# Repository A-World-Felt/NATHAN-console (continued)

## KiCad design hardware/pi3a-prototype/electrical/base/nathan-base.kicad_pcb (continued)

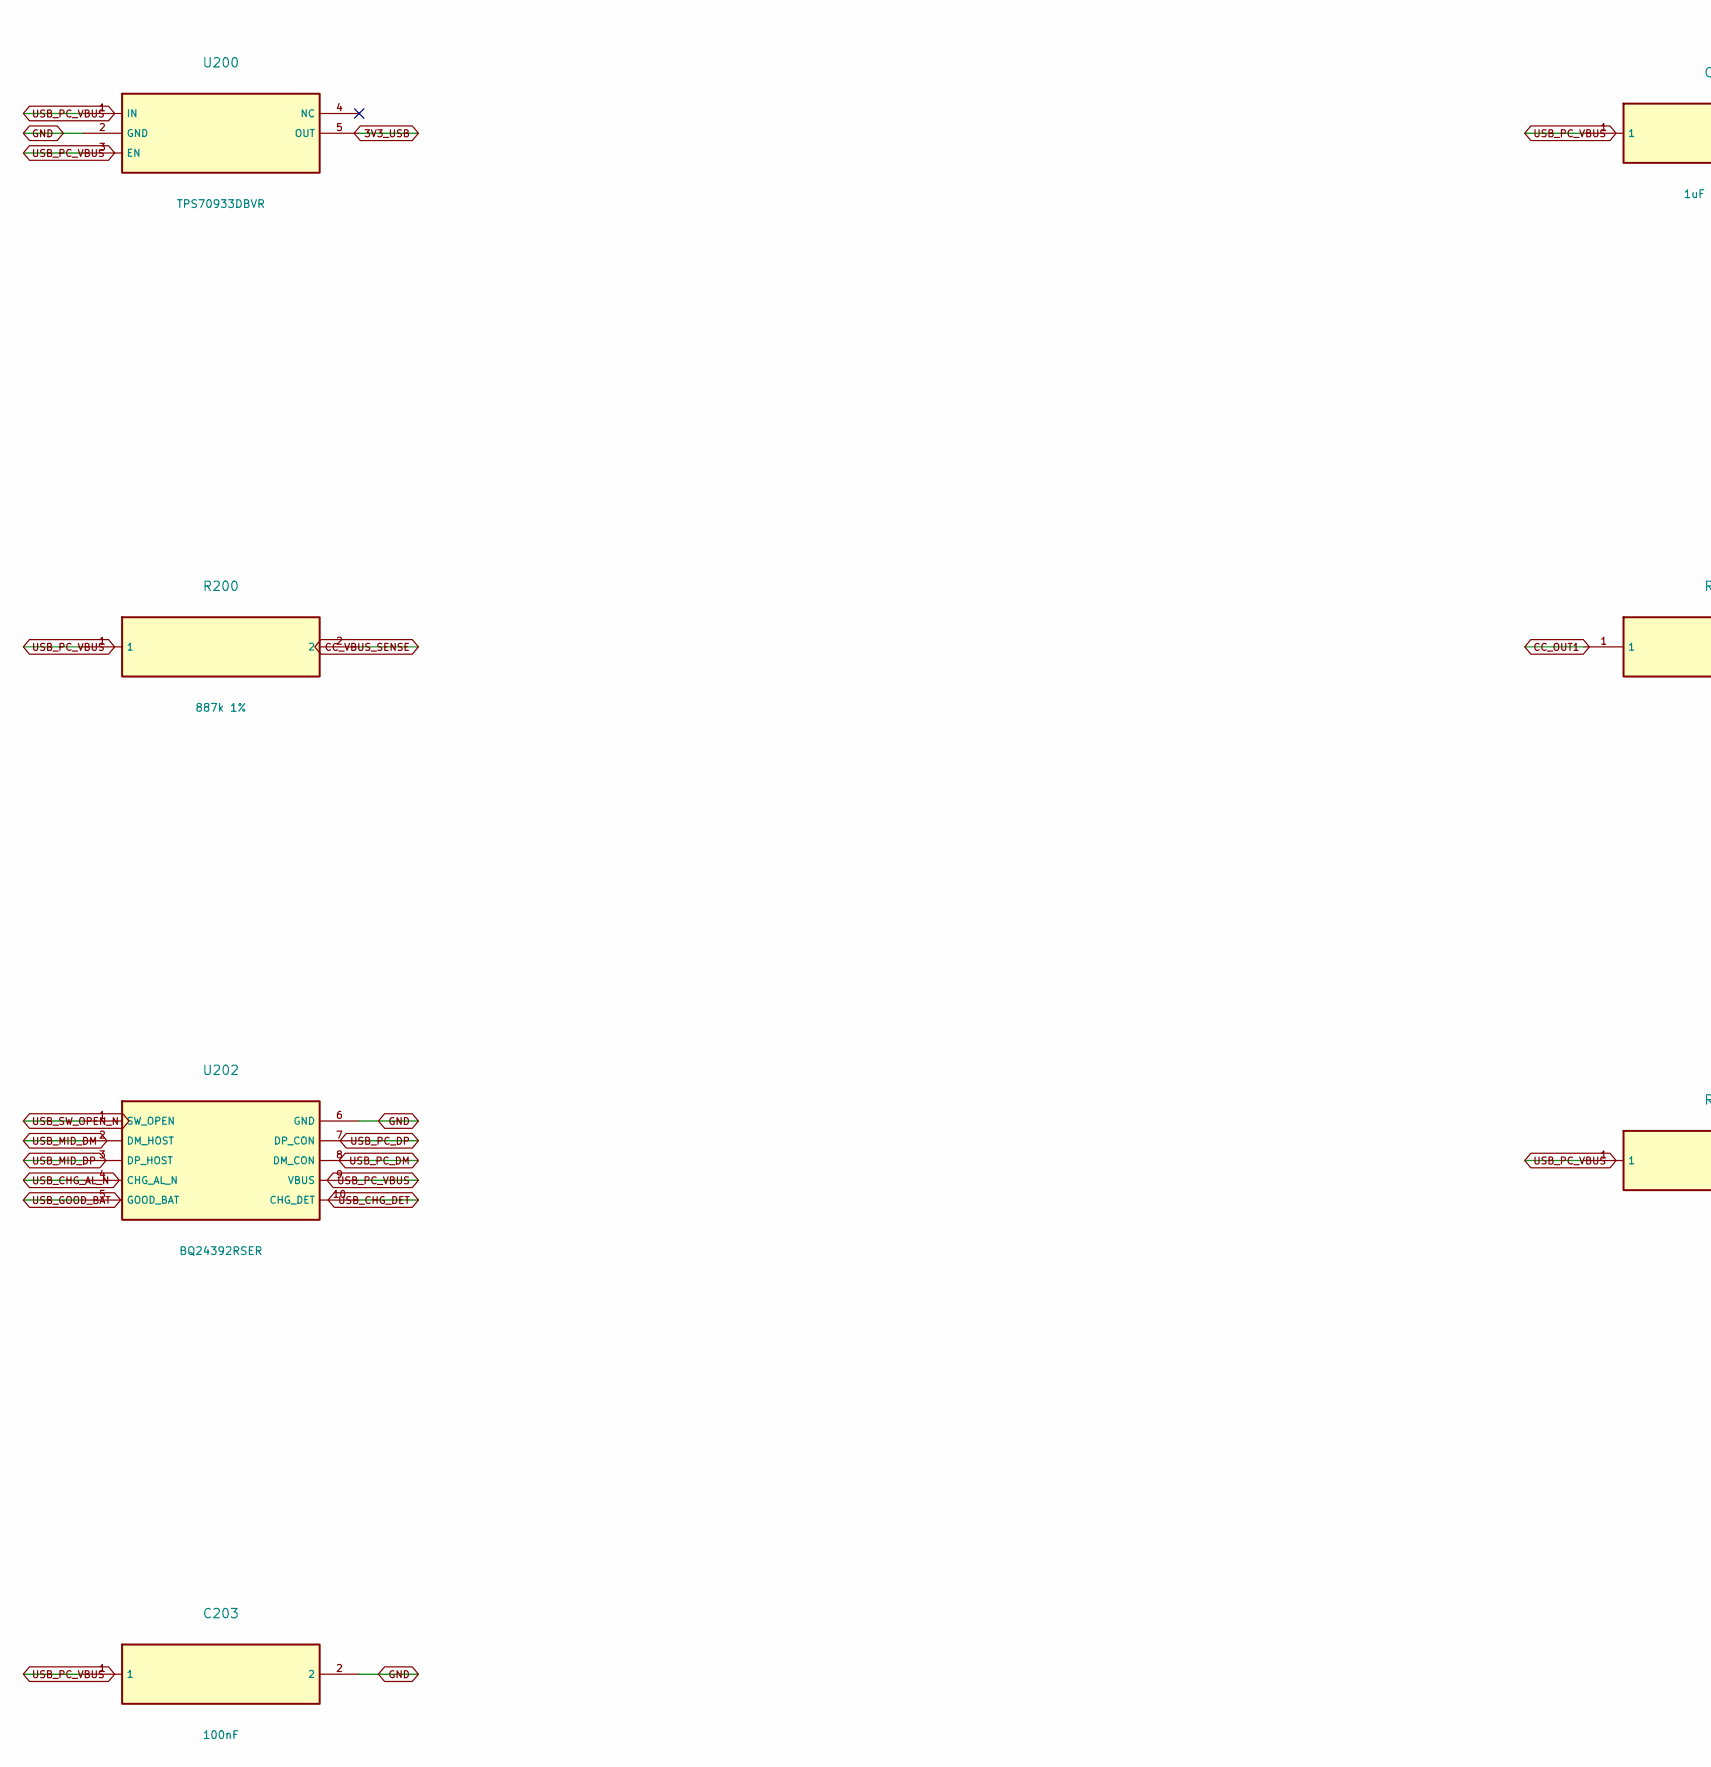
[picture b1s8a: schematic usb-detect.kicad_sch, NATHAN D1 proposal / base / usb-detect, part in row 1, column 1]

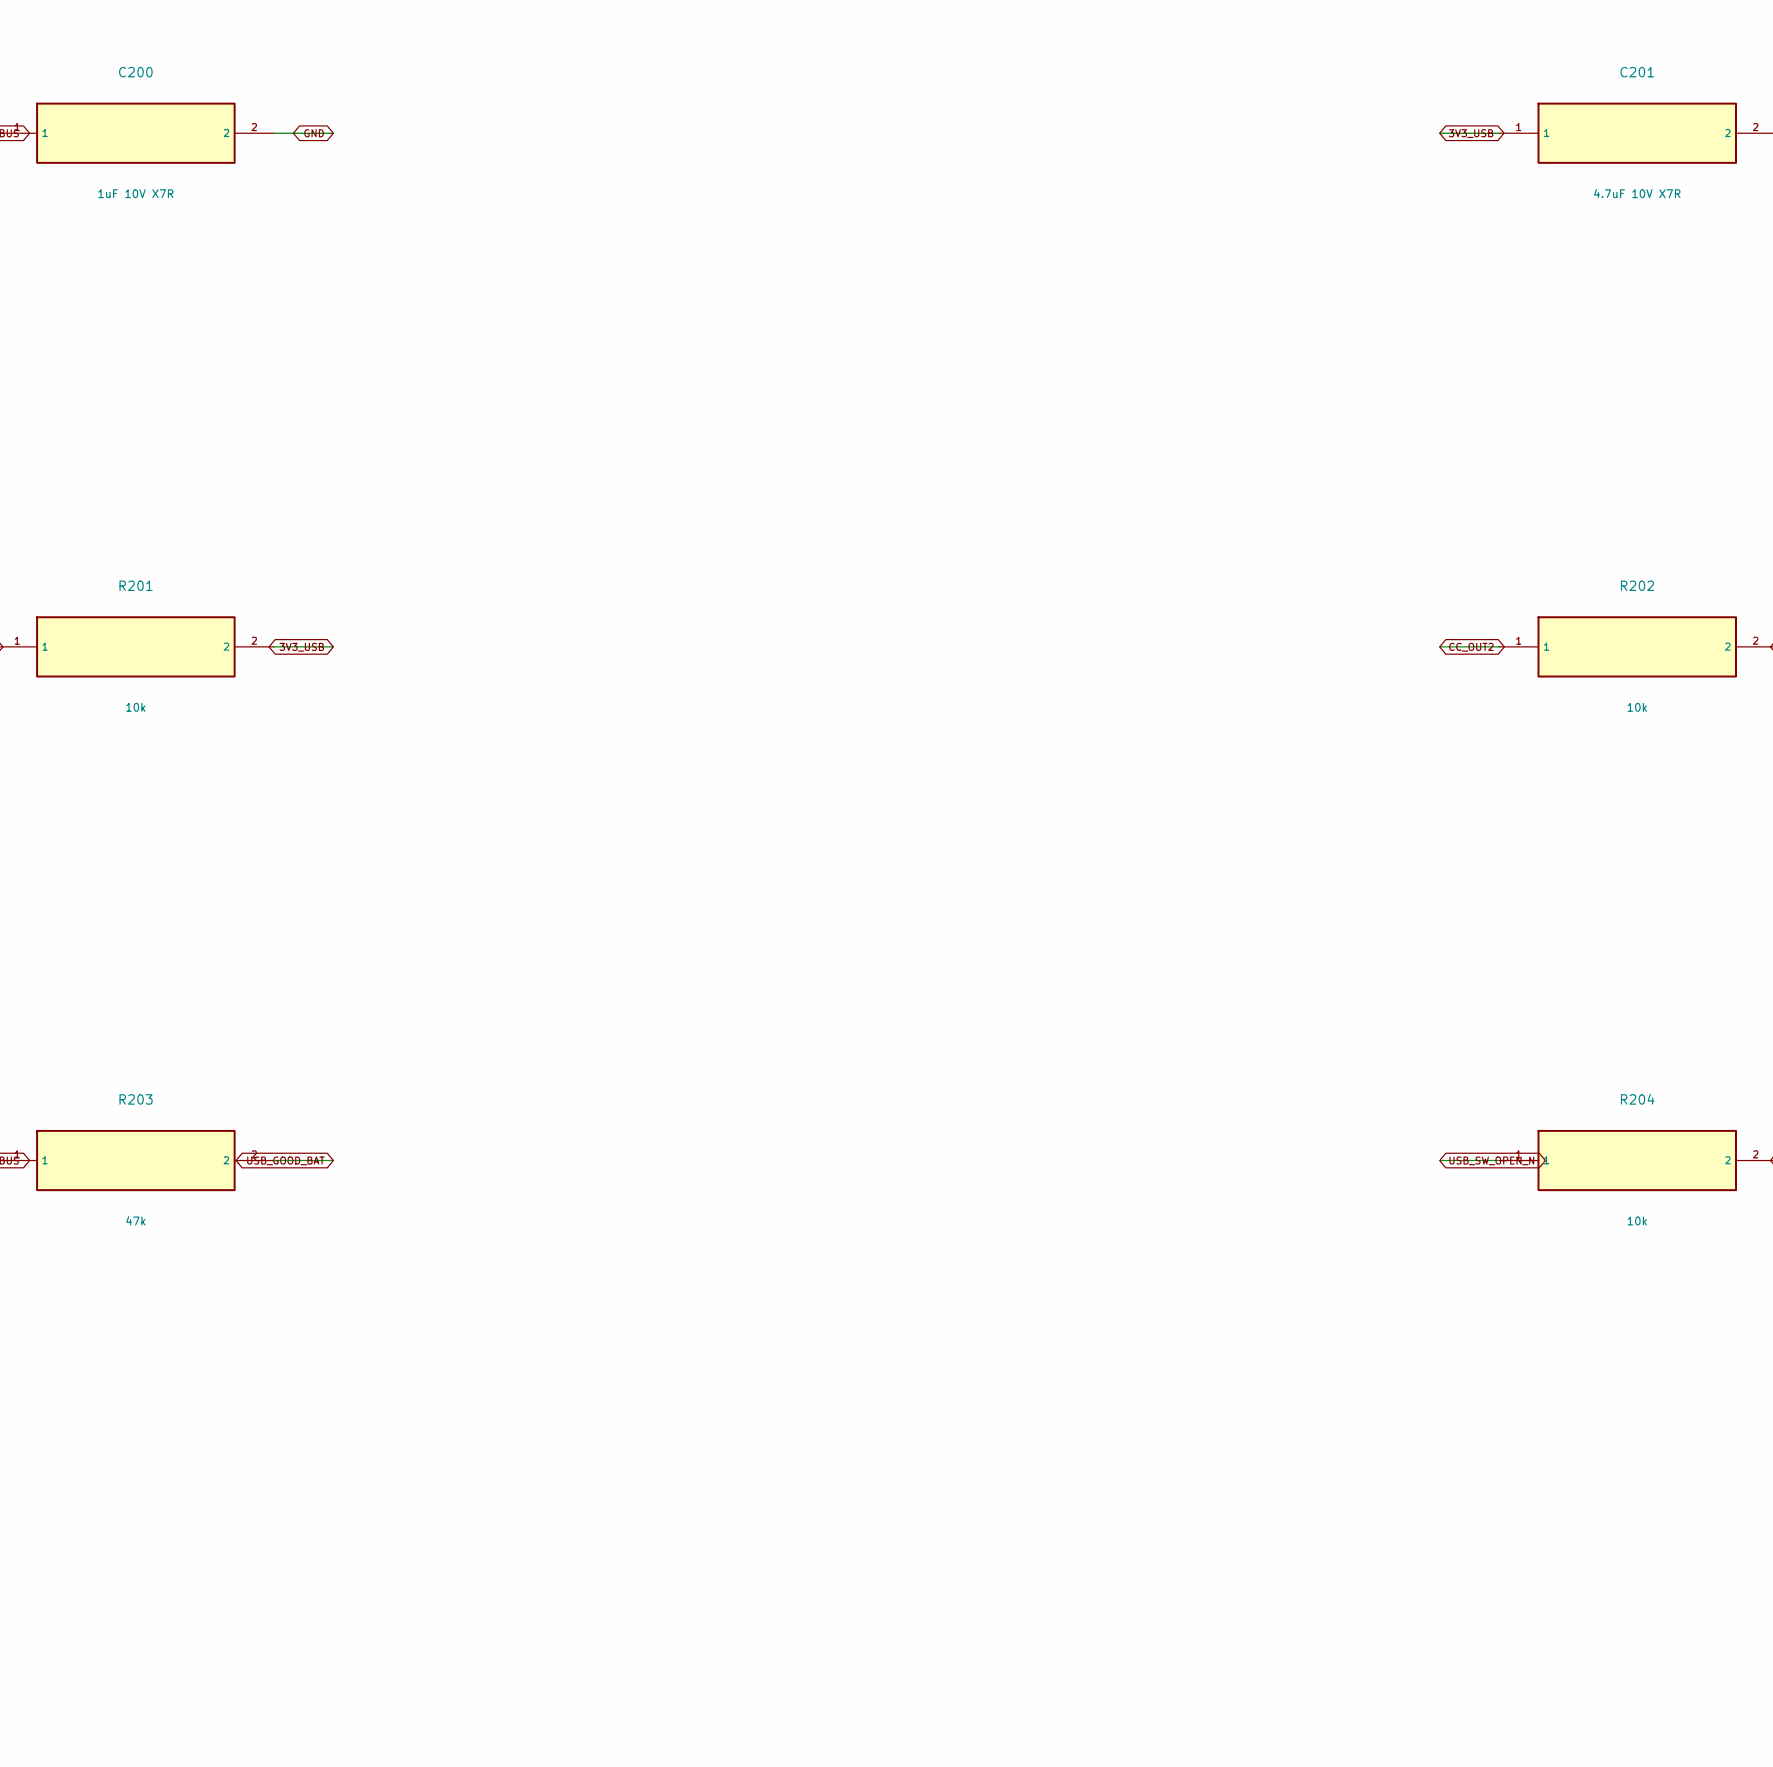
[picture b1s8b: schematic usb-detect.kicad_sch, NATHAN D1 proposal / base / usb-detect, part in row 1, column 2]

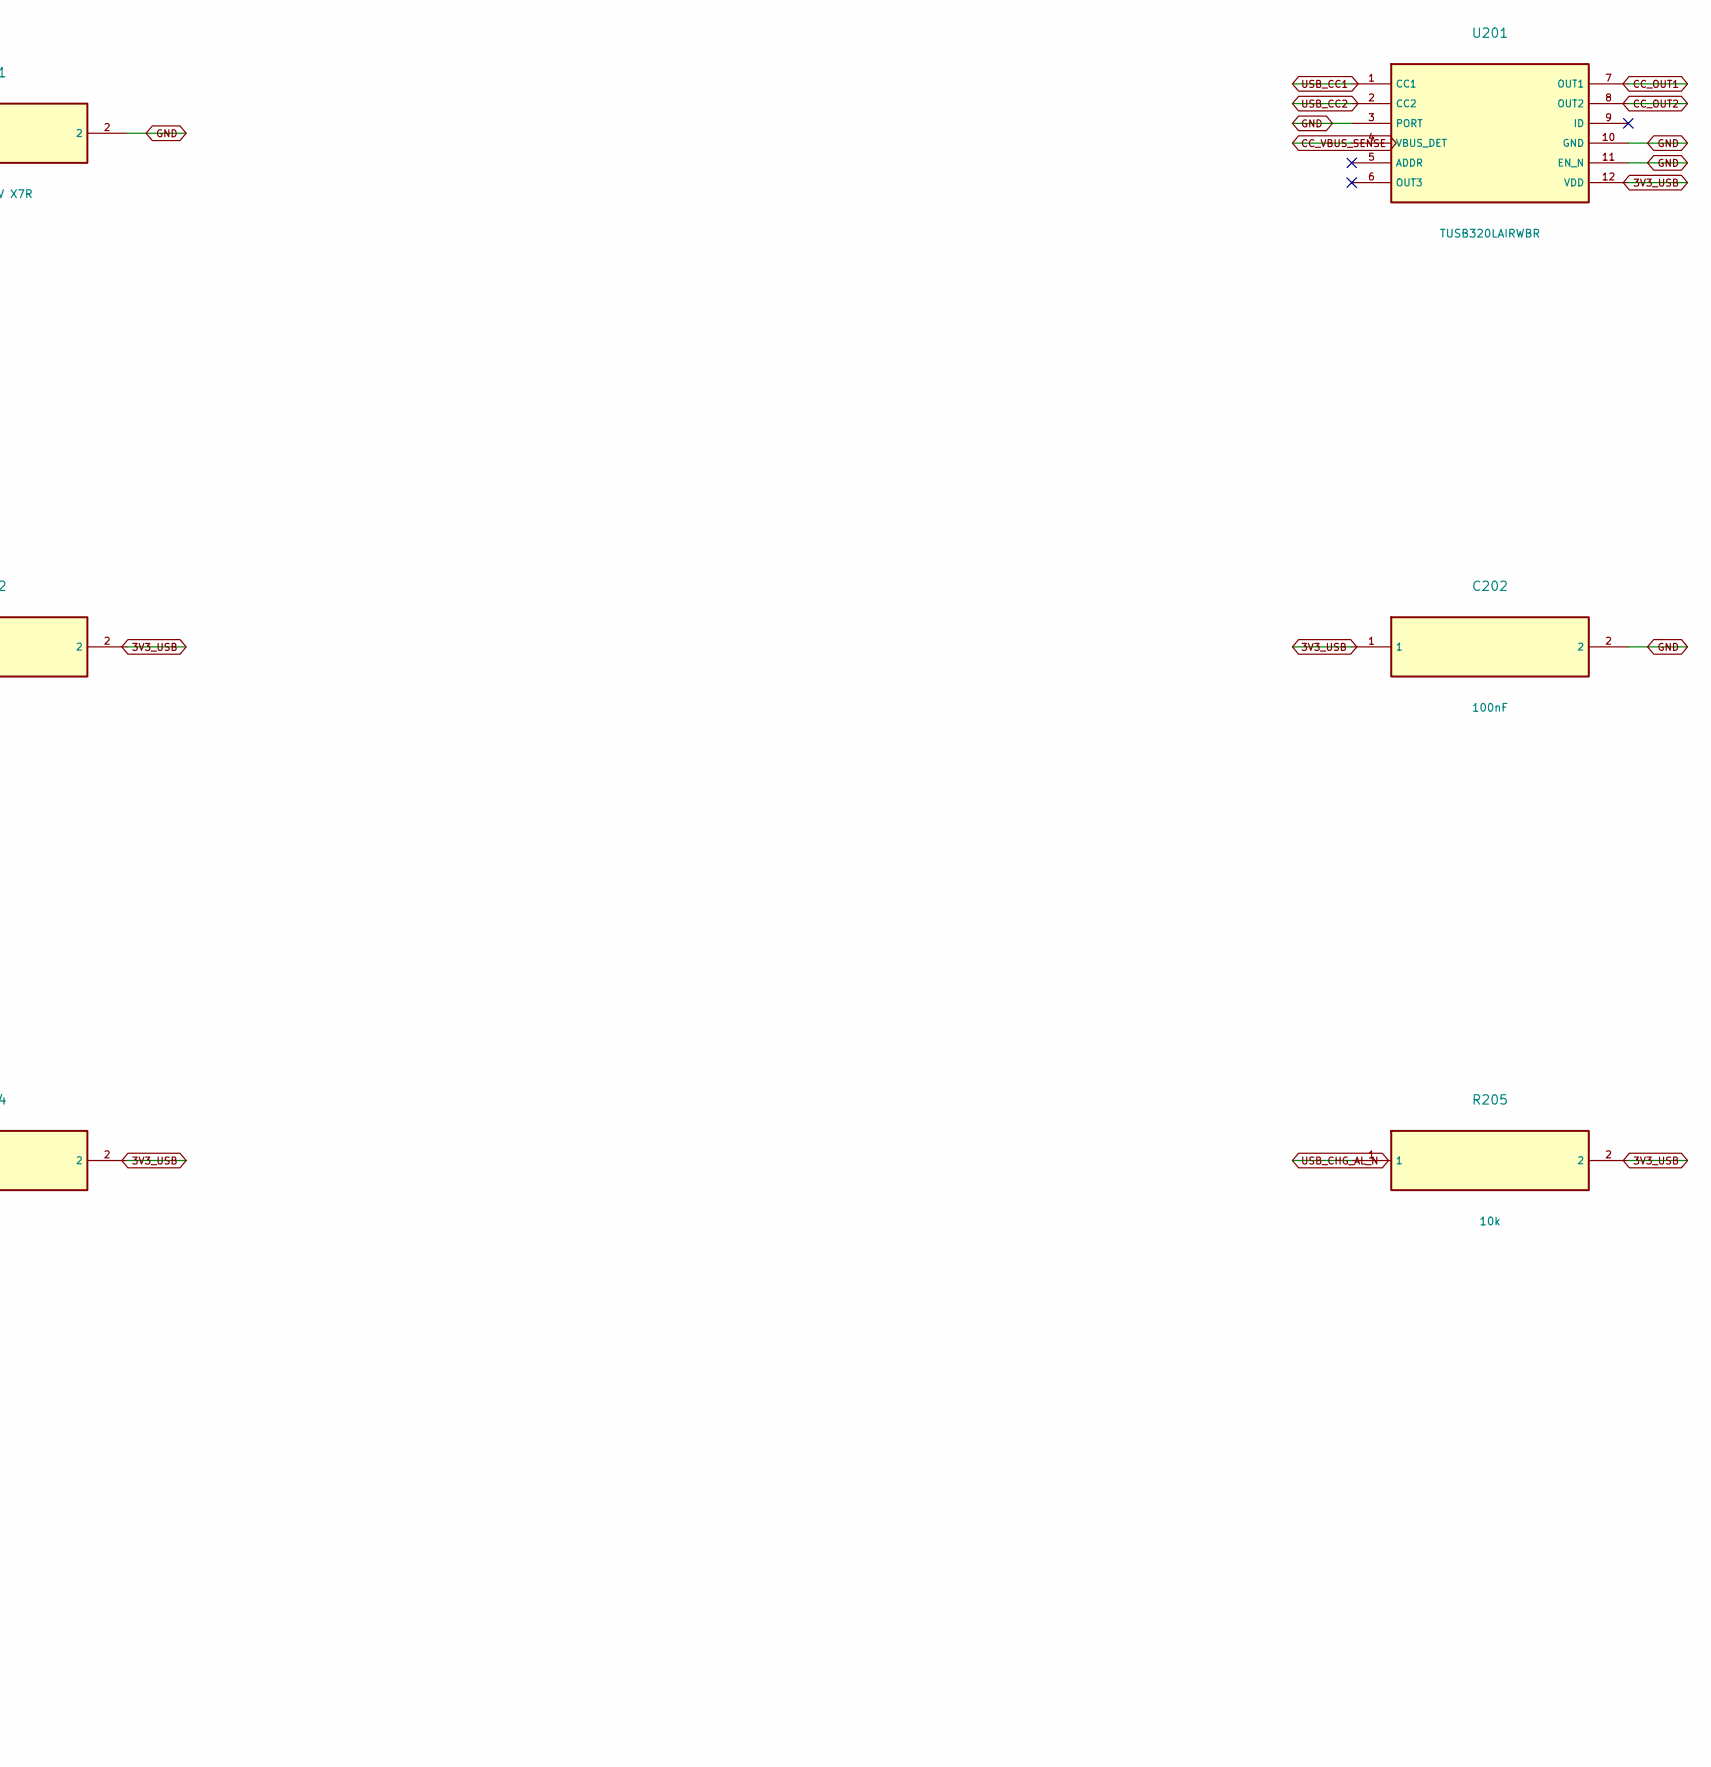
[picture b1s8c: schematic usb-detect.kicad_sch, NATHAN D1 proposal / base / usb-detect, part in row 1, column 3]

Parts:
C200: 1uF 10V X7R; C_0603_1608Metric
C201: 4.7uF 10V X7R; C_0805_2012Metric
C202, C203: 100nF; C_0603_1608Metric
R200: 887k 1%; R_0603_1608Metric
R201, R202, R204, R205: 10k; R_0603_1608Metric
R203: 47k; R_0603_1608Metric
U200: TPS70933DBVR; SOT-23-5
U201: TUSB320LAIRWBR; Texas_X2QFN-12_1.6x1.6mm_P0.4mm
U202: BQ24392RSER; Texas_UQFN-10_1.5x2mm_P0.5mm

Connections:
3V3_USB: C201.1, C202.1, R201.2, R202.2, R204.2, R205.2, U200.5 (OUT), U201.12 (VDD); also elsewhere on the board
CC_OUT1: R201.1, U201.7 (OUT1); also elsewhere on the board
CC_OUT2: R202.1, U201.8 (OUT2); also elsewhere on the board
CC_VBUS_SENSE: R200.2, U201.4 (VBUS_DET)
GND: C200.2, C201.2, C202.2, C203.2, U200.2 (GND), U201.3 (PORT), U201.10 (GND), U201.11 (EN_N), U202.6 (GND); also elsewhere on the board
USB_CC1: U201.1 (CC1); also elsewhere on the board
USB_CC2: U201.2 (CC2); also elsewhere on the board
USB_CHG_AL_N: R205.1, U202.4 (CHG_AL_N); also elsewhere on the board
USB_CHG_DET: U202.10 (CHG_DET); also elsewhere on the board
USB_GOOD_BAT: R203.2, U202.5 (GOOD_BAT)
USB_MID_DM: U202.2 (DM_HOST); also elsewhere on the board
USB_MID_DP: U202.3 (DP_HOST); also elsewhere on the board
USB_PC_DM: U202.8 (DM_CON); also elsewhere on the board
USB_PC_DP: U202.7 (DP_CON); also elsewhere on the board
USB_PC_VBUS: C200.1, C203.1, R200.1, R203.1, U200.1 (IN), U200.3 (EN), U202.9 (VBUS); also elsewhere on the board
USB_SW_OPEN_N: R204.1, U202.1 (SW_OPEN); also elsewhere on the board

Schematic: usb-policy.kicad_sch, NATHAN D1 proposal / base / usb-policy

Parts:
C206, C207, C208, C209, C210, C211: 100nF; C_0603_1608Metric
R206, R207: 1k; R_0603_1608Metric
R208, R209: 4.7k; R_0603_1608Metric
R210, R211: 10k; R_0603_1608Metric
U206, U210: SN74LVC2G04DBVR; SOT-23-6
U207, U211: SN74LVC2G08DCUR; VSSOP-8_2.3x2mm_P0.5mm
U208: SN74LVC1G74DCUR; VSSOP-8_2.3x2mm_P0.5mm
U209: SN74LVC1G32DBVR; SOT-23-5

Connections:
3V3_USB: C206.1, C207.1, C208.1, C209.1, C210.1, C211.1, U206.5 (VCC), U207.8 (VCC), U208.2 (D), U208.7 (PRE_N), U208.8 (VCC), U209.5 (VCC), U210.5 (VCC), U211.8 (VCC); also elsewhere on the board
CC_OUT1: U210.1 (1A), U211.2 (1B); also elsewhere on the board
CC_OUT2: U210.3 (2A); also elsewhere on the board
CC_OUT2_LOW: U210.4 (2Y), U211.6 (2B)
GND: C206.2, C207.2, C208.2, C209.2, C210.2, C211.2, R208.2, R209.2, R210.2, R211.2, U206.2 (GND), U207.4 (GND), U208.4 (GND), U209.3 (GND), U210.2 (GND), U211.4 (GND); also elsewhere on the board
USB_CC_3A: U211.3 (2Y); also elsewhere on the board
USB_CC_POWER: R211.1, U210.6 (1Y), U211.5 (2A); also elsewhere on the board
USB_CHARGE_ALLOWED: U206.4 (2Y), U207.6 (2B)
USB_CHARGE_CLOCK: R207.1; also elsewhere on the board
USB_CHARGE_RUN: R206.1; also elsewhere on the board
USB_CHG_AL_N: U206.3 (2A); also elsewhere on the board
USB_CHG_DET: U209.1 (A); also elsewhere on the board
USB_CLOCK_IN: R207.2, R209.1, U208.1 (CLK)
USB_DATA_ACTIVE: U206.6 (1Y), U207.1 (1A)
USB_GRANT_CLEAR_N: U207.7 (1Y), U208.6 (CLR_N)
USB_LEGACY_EN: R210.1, U211.7 (1Y); also elsewhere on the board
USB_LEGACY_REQUEST: U207.3 (2Y), U211.1 (1A)
USB_REQUEST: U207.5 (2A), U209.4 (Y)
USB_RUN_IN: R206.2, R208.1, U207.2 (1B)
USB_SDP_GRANT: U208.5 (Q), U209.2 (B)
USB_SW_OPEN_N: U206.1 (1A); also elsewhere on the board

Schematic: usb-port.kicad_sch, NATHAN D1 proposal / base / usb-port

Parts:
D200, D201: TPD2E2U06DRLR; SOT-553
J120: USB4105-GF-A; USB_C_Receptacle_GCT_USB4105-xx-A_16P_TopMnt_Horizontal

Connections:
GND: D200.4 (GND), D201.4 (GND), J120.A1, J120.A12, J120.B1, J120.B12, J120.S1; also elsewhere on the board
USB_CC1: D201.3 (IO1), J120.A5; also elsewhere on the board
USB_CC2: D201.5 (IO2), J120.B5; also elsewhere on the board
USB_PC_DM: D200.5 (IO2), J120.A7, J120.B7; also elsewhere on the board
USB_PC_DP: D200.3 (IO1), J120.A6, J120.B6; also elsewhere on the board
USB_PC_VBUS: J120.A4, J120.A9, J120.B4, J120.B9; also elsewhere on the board

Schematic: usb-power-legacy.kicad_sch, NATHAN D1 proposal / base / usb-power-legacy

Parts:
C212: 100nF; C_0603_1608Metric
C213: 1uF 10V X7R; C_0603_1608Metric
R212: 62k 1%; R_0603_1608Metric
U204: TPS2553DBVR; SOT-23-6
U205: LM66100DCKR; SOT-363_SC-70-6

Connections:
GND: C212.2, C213.2, R212.2, U204.2 (GND), U205.2 (GND), U205.5 (ST_UNUSED_GND); also elsewhere on the board
USB_CHARGE_LIMITED: U205.3 (CE), U205.6 (VOUT); also elsewhere on the board
USB_LEGACY_EN: U204.3 (EN); also elsewhere on the board
USB_LEGACY_ILIM: R212.1, U204.5 (ILIM)
USB_LEGACY_LIMITED: C213.1, U204.6 (OUT), U205.1 (VIN)
USB_PC_VBUS: C212.1, U204.1 (IN); also elsewhere on the board

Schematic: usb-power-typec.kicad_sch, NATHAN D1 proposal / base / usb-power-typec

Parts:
C214: 3.3nF C0G; C_0603_1608Metric
C215: 100nF; C_0603_1608Metric
C216: 1uF 10V X7R; C_0603_1608Metric
J121: J121 interface; Power_Pigtail_2Pad
Q200: 2N7002; SOT-23
R213, R214: 2.80k 1%; R_0603_1608Metric
R215: 100k; R_0603_1608Metric
R216: 348k 1%; R_0603_1608Metric
R217: 100k 1%; R_0603_1608Metric
U212: TPS259470ARPWR; TI_RPW0010A

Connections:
GND: C214.2, C215.2, C216.2, J121.2 (GND), Q200.2 (S), R213.2, R215.2, R217.2, U212.8 (GND); also elsewhere on the board
USB_CC_3A: Q200.1 (G), R215.1; also elsewhere on the board
USB_CC_POWER: U212.1 (EN_UVLO); also elsewhere on the board
USB_CHARGE_LIMITED: C216.1, J121.1 (PISUGAR_INPUT_5V), U212.6 (OUT); also elsewhere on the board
USB_DVDT: C214.1, U212.7 (DVDT)
USB_ILIM_EXTRA: Q200.3 (D), R214.2
USB_OVLO: R216.2, R217.1, U212.2 (OVLO)
USB_PC_VBUS: C215.1, R216.1, U212.5 (IN); also elsewhere on the board
USB_TYPEC_ILIM: R213.1, R214.1, U212.9 (ILM)

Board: 4 copper layers, 92 parts (56 on the bottom side), 73 nets, no tracks yet.

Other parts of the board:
H1, H2, H3, H4: MountingHole_2.7mm_M2.5

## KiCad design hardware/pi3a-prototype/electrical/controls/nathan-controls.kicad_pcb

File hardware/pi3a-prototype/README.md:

# NATHAN — prototype Pi 3 A+ à deux PCB

**En pause à la demande d’Arthur pour limiter la consommation.** Checkpoint D1-3, Codex/OpenAI (`nathan_bom` et parent), 22 octobre 2026. Proposition de conception, sans autorisation de fabrication ni jalon déclaré terminé.

## Voir le travail

- [Vue assemblée](mechanical/previews/nathan-review-assembled.png) et [vue éclatée](mechanical/previews/nathan-review-exploded.png).
- [Assemblage FreeCAD](mechanical/assembly/nathan-D1-review.FCStd) et [STEP](mechanical/assembly/nathan-D1-review.step).
- [Commandes KiCad](electrical/controls/nathan-controls.kicad_pro) et [porteuse KiCad](electrical/base/nathan-base.kicad_pro).
- [ADR-0008 proposé](../../docs/decisions/0008-prototype-pi3a-deux-pcb-pisugar.md), [revue USB-C](docs/usb-c-review.md), [reprise Claude](docs/reprise-claude.md).

Les images montrent la géométrie FreeCAD livrée. Largeur nominale 160 mm, hauteur de coque proposée 72 mm : **ébauche épaisse, ergonomie non validée**. Pi, PiSugar, batterie et certains mécanismes sont simplifiés ou représentés par des volumes réservés.

## État exact publié D1-3

| Livrable | État du checkpoint |
|---|---|
| Commandes | 93 composants + 4 fixations, quatre couches, pistes réelles. DRC : **0 erreur, 0 liaison ouverte, 17 avertissements** (7 vias pendants et 10 sérigraphies/bords). |
| Porteuse | 88 composants + 4 fixations, schéma GPIO/audio/USB-C et placement connecté. **257 liaisons ouvertes**, 4 erreurs de dégagement J120, 0 avertissement. Routage non terminé. |
| Schémas | ERC natif observé à zéro message sur les deux cartes. Les preuves et leurs périmètres figurent dans les rapports ; un ERC ne qualifie pas un circuit. |
| PCB/modèle | 337 pastilles numérotées commandes, 371 porteuse : zéro écart de net. Doublons physiques documentés. |
| Assemblage | STEP des deux cartes synchronisés, 58 formes valides. Huit paires ciblées sans intersection exacte, dont PCB/coques et commandes/L2. **Intersection des deux coques : 3,712 mm³**, à corriger. |

Le [manifeste D1-3](validation/checkpoint-d1-3.json) identifie les cartes, STEP, FCStd et rapports par SHA-256. [Revue mécanique indépendante](validation/parent/assembly-review-3.json). FCStd livré : `1a8ec46981c5897a12d664be2637b82b00acf471602682b01969a5fc0f7a3f11`.

`pcb/`, les sources OpenSCAD et `parameters/design.json` sont D0.1. Les projets D1 se trouvent dans `electrical/`, leur empilement dans `parameters/assembly-d1.json`. Ne pas mélanger les révisions de connectique.

## À reprendre

USB-C remplace la mention initiale micro-B selon la dernière précision d’Arthur. VBUS rejoint l’entrée du PiSugar, sa sortie alimente le Pi. Charge et utilisation simultanées dépendent du budget disponible. Batterie vide sur PC standard, logiciel d’autorisation de charge, transitions de courant, protection de la limite PiSugar 5,2 V et intégrité USB restent à résoudre ou qualifier.

La puissance des commandes doit être revue : tronc 5 V de 0,2 mm et boucle de convertisseur à améliorer. Les essais locaux de déplacement/découplage sont incomplets et **ne sont pas intégrés** à ce checkpoint. Le routage de la porteuse reste à faire.

Finaliser jonction de coque, ouvertures USB-C/casque, capteurs, ressorts, butées, câbles et dimensions du kit réel. Aucun essai matériel, thermique, autonomie, audio, haptique, USB ou ergonomie n’a été réalisé. Aucun export de production n’est fourni.

## Reproduction et précautions de reprise

KiCad 8.0.2 et FreeCAD 1.1.4 portable ont été utilisés. Aucun exécutable n’est distribué. Les générateurs `build_connected_*.py` écrasent les PCB : travailler dans une copie. Les scripts de routage sont les étapes historiques, pas une reconstruction complète qualifiée.

```powershell
$env:HF_HUB_OFFLINE = '1'
$env:PYTHONDONTWRITEBYTECODE = '1'
python tools/run_native_check.py erc controls
python tools/run_native_check.py erc base
```

Les contrôles natifs sont bornés et utilisent un profil local préparé depuis la distribution KiCad. Voir [l’incident KiCad](docs/incident-kicad.md). Les rapports intermédiaires restent diagnostiques : le manifeste indique ceux du checkpoint. Le dépôt historique et le classeur BOM original ne sont pas modifiés.

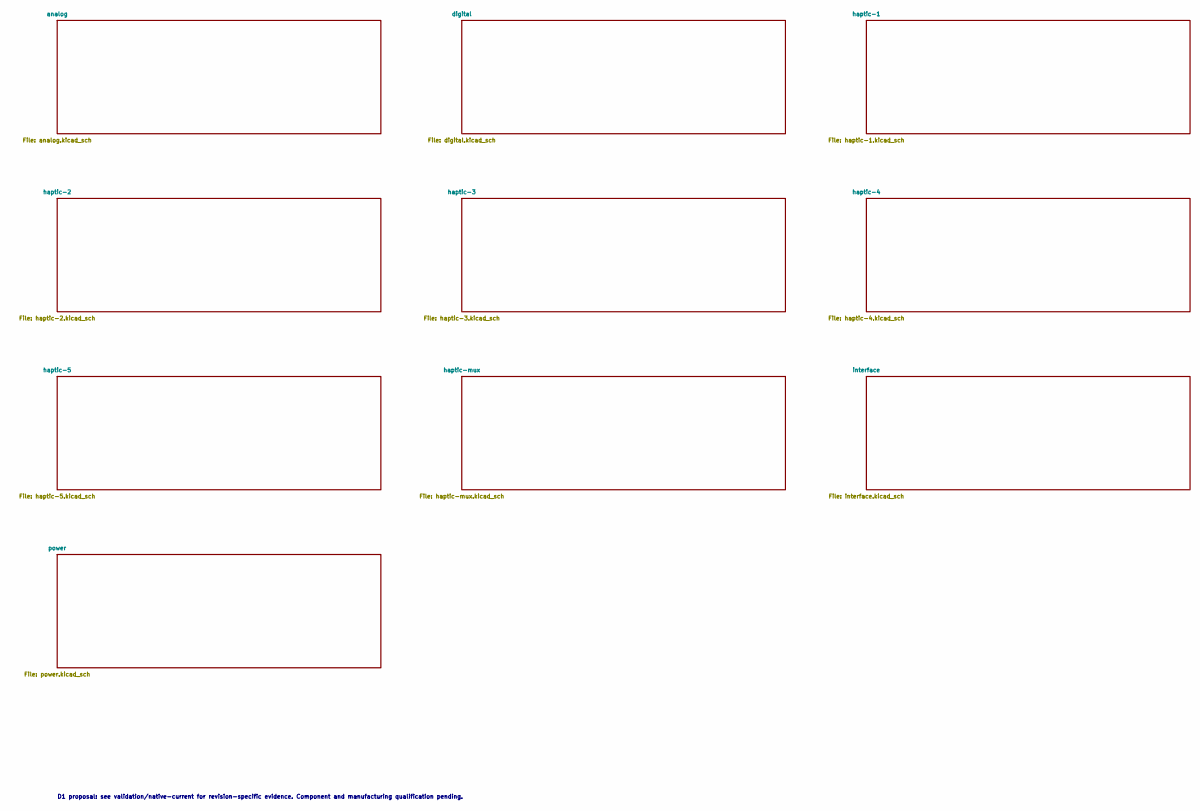
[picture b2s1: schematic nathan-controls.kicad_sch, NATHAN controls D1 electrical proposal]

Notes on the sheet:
D1 proposal: see validation/native-current for revision-specific evidence. Component and manufacturing qualification pending.
